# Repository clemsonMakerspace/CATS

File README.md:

CATS
====

The Clemson (Machinery) Access Tracking System, or CATS, is a [Creative Inquiry](http://www.clemson.edu/academics/programs/creative-inquiry/) project at Clemson University.

The goal of the project is to come up with an open-source system that can track and control machine access
at the Makerspaces on the campus.  As we work on the design process, we document our progress in our blog,
which you can find [here](http://ci.clemson.edu/blogs/cats/).

----

### Dependencies

This is a Python 3.x program dependent on the following libraries:
   1. `sys` - Python sys Libary
   2. `time` - Python time library
   3. `pymysql` - Python MySQL client
   4. `datetime` - Python datetime library
   5. `os` - Python os library (Python operating system interface)
   6. `RPi.GPIO` - package for controlling Rasberry Pi GPIO
   7. `string` - Python string library
   8. `InputDevice from evdev` - function from evdev package for Linux inputs
   9. `select from select` - Python select function from select library
   
These dependencies can be installed with the 'setup.sh' shell script found within.

### Configuration

TODO

### Usage

TODO

### License

The Clemson (Machinery) Access Tracking System is free software: you can 
redistribute it and/or modify it under the terms of the GNU Lesser General 
Public License as published by the Free Software Foundation, either version 
3 of the License, or (at your option) any later version.

The Clemson (Machinery) Access Tracking System is distributed in the hope 
that it will be useful, but WITHOUT ANY WARRANTY; without even the implied 
warranty of MERCHANTABILITY or FITNESS FOR A PARTICULAR PURPOSE.  See the
GNU Lesser General Public License for more details.

You should have received a copy of the GNU Lesser General Public License
along with this program.  If not, see <http://www.gnu.org/licenses/>

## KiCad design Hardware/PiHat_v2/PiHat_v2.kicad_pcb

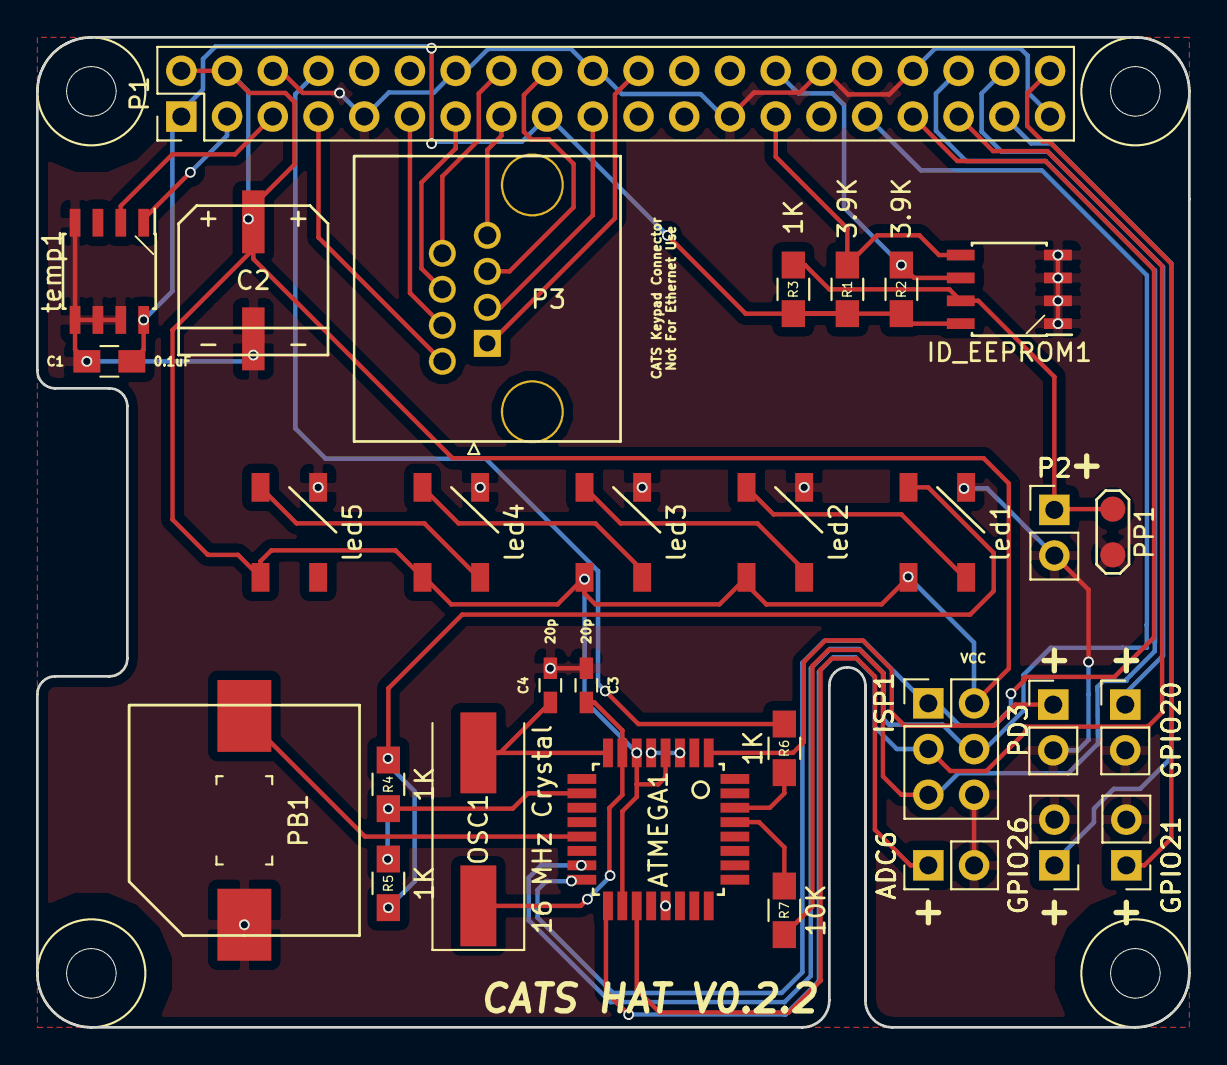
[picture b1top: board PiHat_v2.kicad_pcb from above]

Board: 2 copper layers, 64.0 x 55.0 mm, 35 parts (0 on the bottom side), 37 nets.

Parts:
ADC6: aux_conn; Pin_Header_Straight_1x02_Pitch2.54mm
ATMEGA1: ATMEGA328P-A; ATMEGA328P
C1: 0.1uF; C_0805_HandSoldering
C2: 1000uF; AluCap_8mmDia_Nichicon
C3, C4: 20p; C_0603_HandSoldering
GPIO20, GPIO21, GPIO26: aux_conn; Pin_Header_Straight_1x02_Pitch2.54mm
ID_EEPROM1: CAT24C32; SOIC-8_3.9x4.9mm_Pitch1.27mm
ISP1: ISP; Pin_Header_Straight_2x03_Pitch2.54mm
MountHole1, MountHole2, MountHole3, MountHole4: CONN_01X01; raspiMountingHole
OSC1: 16 MHz Crystal; Crystal_SMD_HC49-SD
P1: RPiGPIO; Pin_Header_Straight_2x20_Pitch2.54mm
P2: CONN_01X02; Pin_Header_Straight_1x02_Pitch2.54mm
P3: CONN_01X08; Keypad_Ethernet
PB1: Piezo; Piezo_CT-1205h-smt
PD3: aux_conn; Pin_Header_Straight_1x02_Pitch2.54mm
PP1: horizTest; Test_Point_2Pads
R1, R2: 3.9K; R_0805_HandSoldering
R3, R4, R5, R6: 1K; R_0805_HandSoldering
R7: 10K; R_0805_HandSoldering
led1, led2, led3, led4, led5: Neo_LED_RGB_IC; Neo_RGB_LED
temp1: LM75BD; SOIC-8_3.9x4.9mm_Pitch1.27mm

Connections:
+3V3: C1.1, ID_EEPROM1.8, P1.1, P1.17, R1.1, R2.1, R3.1, temp1.8
+5V: ATMEGA1.4, ATMEGA1.6, ATMEGA1.18, C2.1, ISP1.2, P1.2, P1.4, led1.VDD, led2.VDD, led3.VDD, led4.VDD, led5.VDD
/ADC6: ADC6.1, ATMEGA1.19
/GPIO2: P1.3, temp1.1
/GPIO3: P1.5, temp1.2
/GPIO4: P1.7, P3.2
/GPIO6: ATMEGA1.15, ISP1.4, P1.31
/GPIO10: P1.19, P3.3
/GPIO13: ATMEGA1.16, ISP1.1, P1.33
/GPIO16: ISP1.5, P1.36, R7.1
/GPIO17: P1.11, P3.4
/GPIO19: ATMEGA1.17, ISP1.3, P1.35
/GPIO20: GPIO20.1, P1.38
/GPIO21: GPIO21.1, P1.40
/GPIO22: P1.15, P3.7
/GPIO23: P1.16, P3.8
/GPIO24: P1.18, P3.5
/GPIO25: P1.22, P3.1
/GPIO26: GPIO26.1, P1.37
/GPIO27: P1.13, P3.6
/ID_SC: ID_EEPROM1.6, P1.28, R2.2
/ID_SD: ID_EEPROM1.5, P1.27, R1.2
/PB1: ATMEGA1.13, PB1.1
/PD3: ATMEGA1.1, PD3.1
/PD6: R4.1, R5.1, led1.DIN
/UART_TXD: P1.8, R6.1
GND: ADC6.2, ATMEGA1.3, ATMEGA1.5, ATMEGA1.21, C1.2, C2.2, C3.1, C4.1, GPIO20.2, GPIO21.2, GPIO26.2, ID_EEPROM1.1, ID_EEPROM1.2, ID_EEPROM1.3, ID_EEPROM1.4, ISP1.6, P1.6, P1.9, P1.14, P1.20, P1.25, P1.30, P1.34, P1.39, P2.2, PB1.2, PD3.2, PP1.1, led1.VSS, led2.VSS, led3.VSS, led4.VSS, led5.VSS, temp1.4, temp1.5, temp1.6, temp1.7
unnamed: ATMEGA1.7, C3.2, OSC1.1
unnamed: ATMEGA1.8, C4.2, OSC1.2
unnamed: ATMEGA1.10, R4.2, R5.2
unnamed: ATMEGA1.29, R7.2
unnamed: ATMEGA1.30, R6.2
unnamed: ID_EEPROM1.7, P2.1, PP1.2, R3.2
unnamed: led1.DOUT, led2.DIN
unnamed: led2.DOUT, led3.DIN
unnamed: led3.DOUT, led4.DIN
unnamed: led4.DOUT, led5.DIN

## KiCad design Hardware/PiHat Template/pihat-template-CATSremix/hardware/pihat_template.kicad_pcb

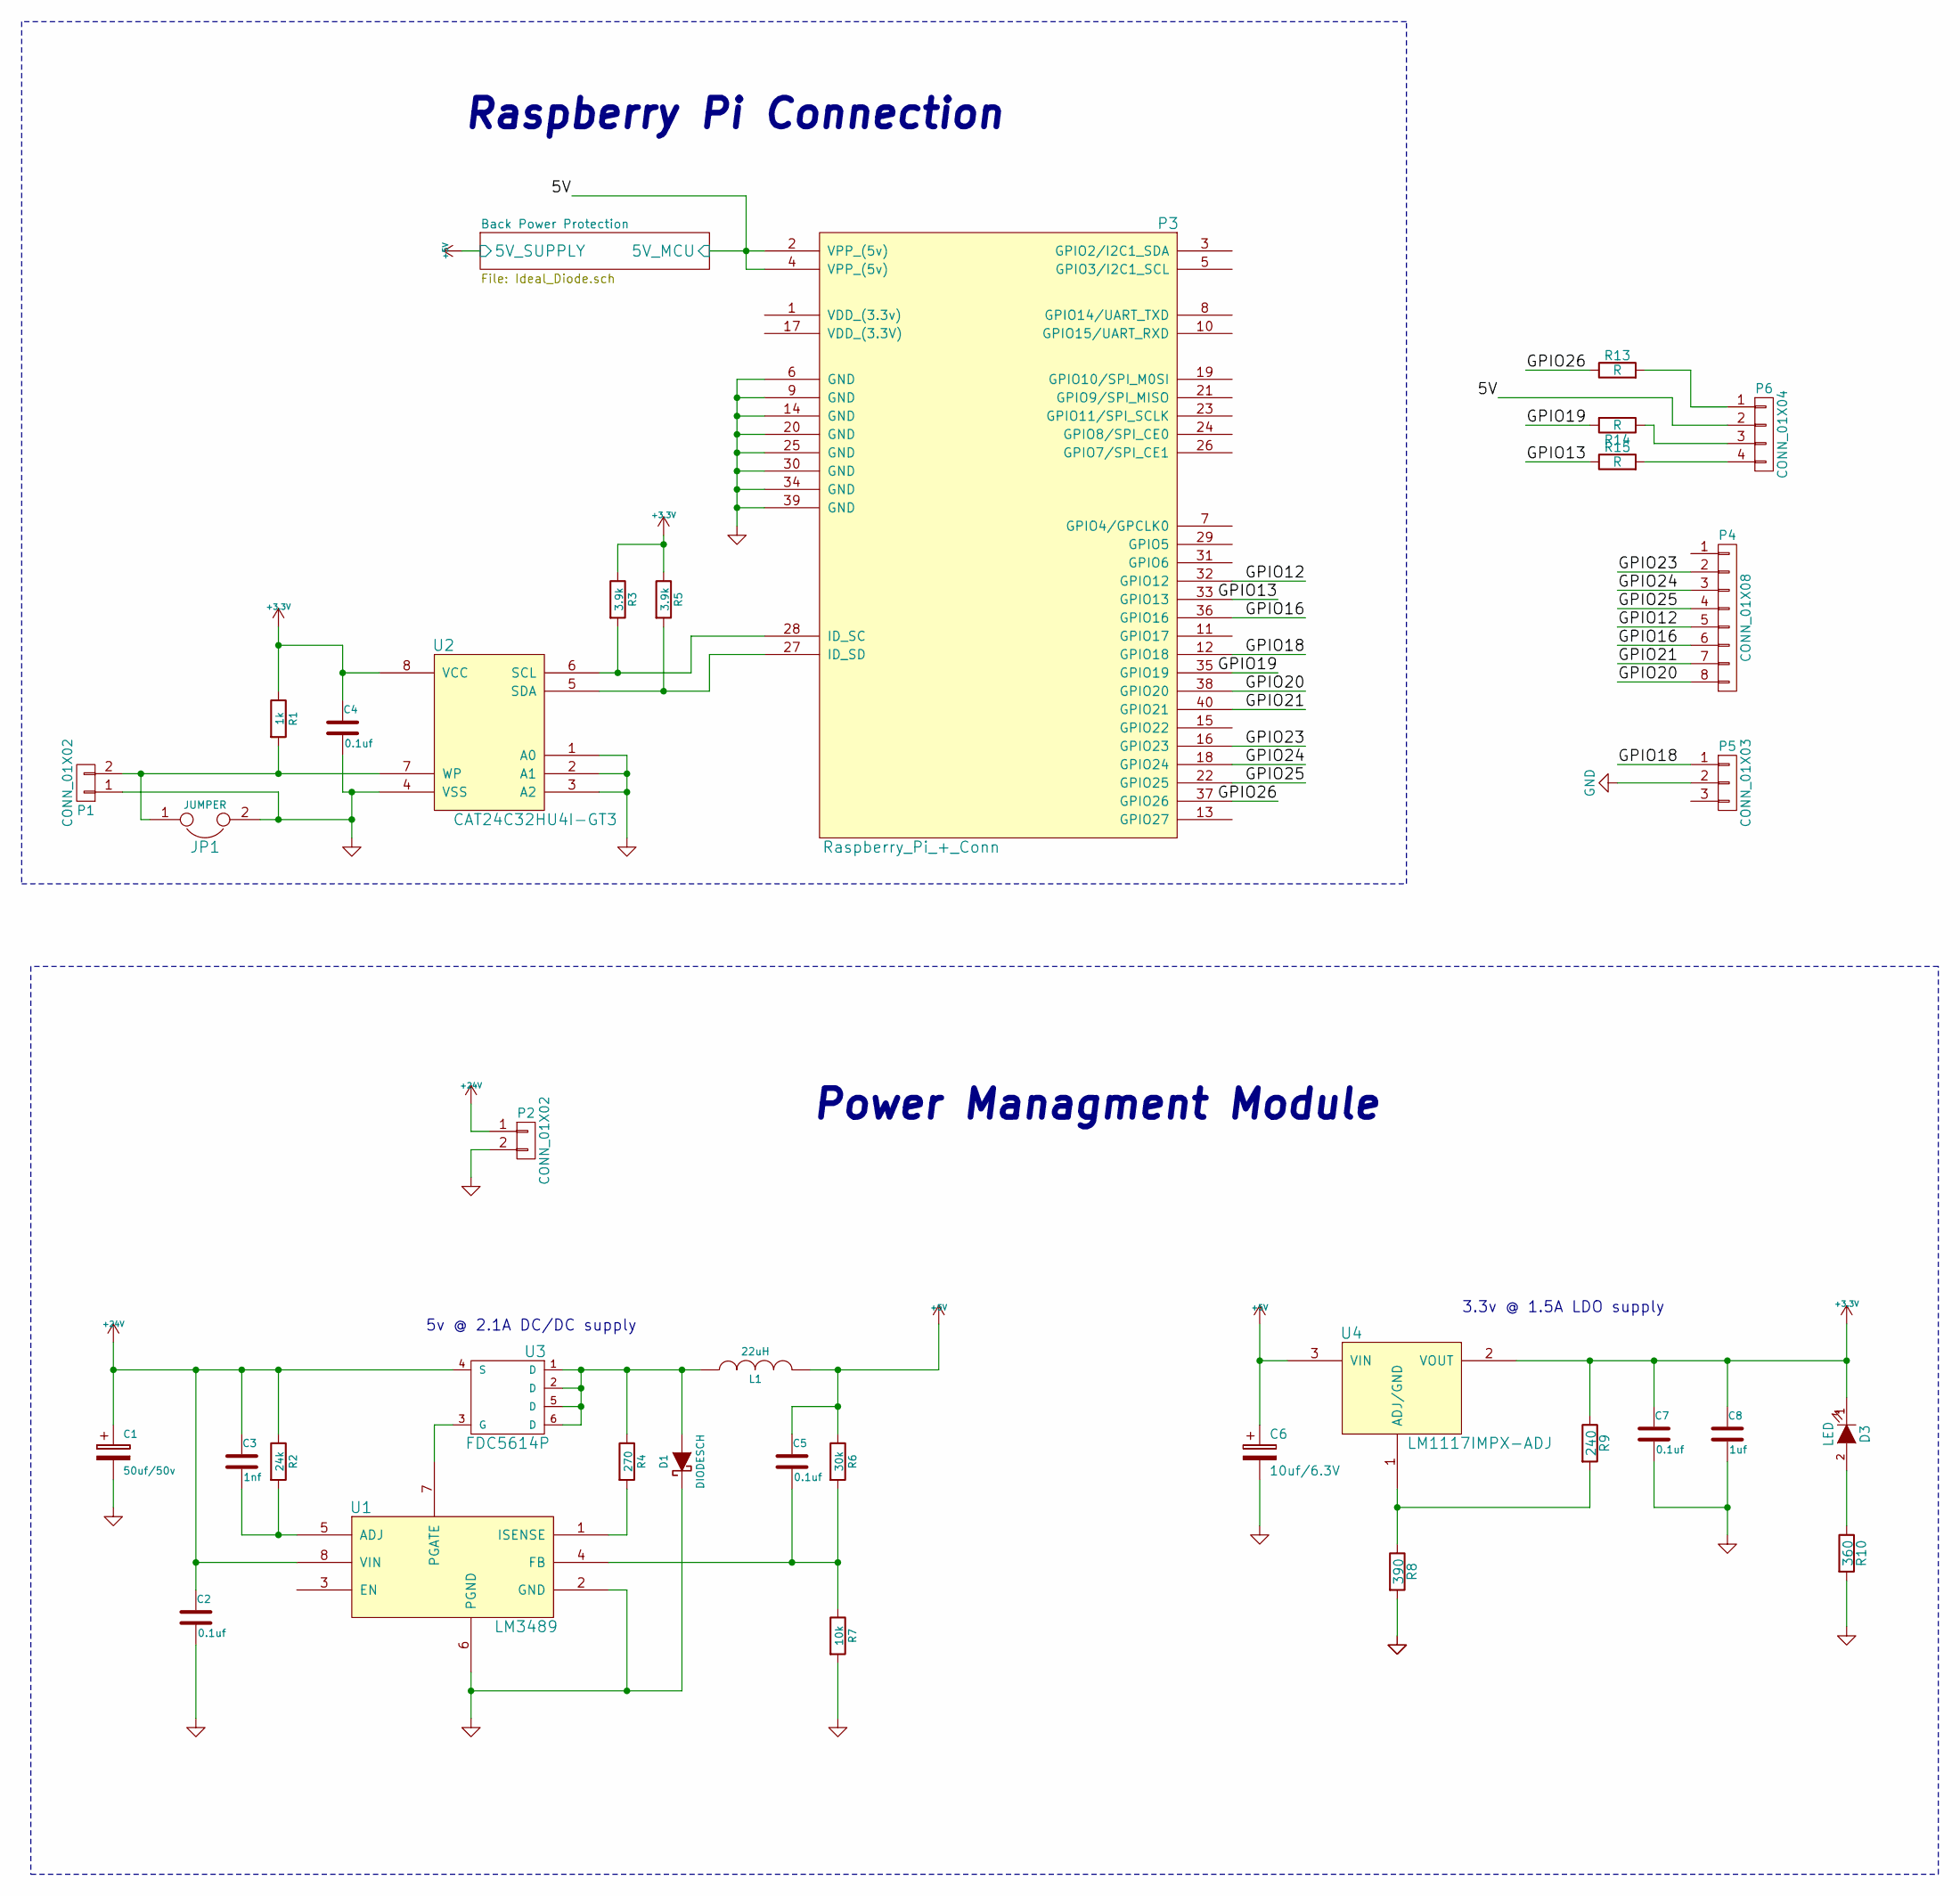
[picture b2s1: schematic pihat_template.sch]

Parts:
C1: 50uf/50v; c_elec_6.3x7.7; Mouser Part No. 647-UUR1H470MCL6GS
C2, C4, C5, C7: 0.1uf; c_0402; Mouser Part No. 810-C1005X5R1H104K
C3: 1nf; c_0402; Mouser Part No. 810-C1005C0G2A102J5C
C6: 10uf/6.3V; c_elec_4x5.3; Mouser Part No. 5985-AVS16V100-F
C8: 1uf; c_0402; Mouser Part No. 810-C1005X5R1H104K
D1: DIODESCH; do214aa; Mouser Part No. 512-MBRS140
D3: LED; Led_0603; Mouser Part No. 743-HT-191USD
JP1: JUMPER; r_0603
L1: 22uH; inductor_smd_8x5mm; Mouser Part No. 652-SRN8040-220M
P1: CONN_01X02; pin_strip_2
P2: CONN_01X02; mkds_1,5-2; Mouser Part No. 651-1904383
P3: Raspberry_Pi_+_Conn; vasch_strip_20x2; Mouser Part No. 517-30340-6002
P4: CONN_01X08; Socket_Strip_Straight_1x08
P5: CONN_01X03; Socket_Strip_Straight_1x03
P6: CONN_01X04; Socket_Strip_Straight_1x04
R1: 1k; r_0402; Mouser Part No. 754-RR0510P-102D
R2: 24k; r_0402; Mouser Part No. 71-CRCW0402-24K-E3
R3, R5: 3.9k; r_0402; Mouser Part No. 71-CRCW04023K90FKED
R4: 270; r_0402; Mouser Part No. 667-ERJ-P6WJ271V
R6: 30k; r_0402; Mouser Part No. 594-MCT06030C3002FP5
R7: 10k; r_0402; Mouser Part No. 71-CRCW0603-10K-E3
R8: 390; r_0402; Mouser Part No. 594-MCT06030C3900FP5
R9: 240; r_0402; Mouser Part No. 754-RR0816P-241D
R10: 360; r_0402; Mouser Part No. 71-CRCW0603316RFKEB
R13, R14, R15: R; Resistor_Vertical_RM5mm
U1: LM3489; msoic-8; Mouser Part No. 926-LM3489MM/NOPB
U2: CAT24C32HU4I-GT3; tssop-8; Mouser Part No. 698-CAT24C32YI-GT3
U3: FDC5614P; sot23-6; Mouser Part No. 512-FDC5614P
U4: LM1117IMPX-ADJ; sot223; Mouser Part No. 926-M1117IMPXADJNOPB

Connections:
+3V3: C4.1, C7.1, C8.1, D3.1 (K), R1.1, R3.1, R5.1, R9.1, U2.8 (VCC), U4.2 (VOUT)
+5V: C5.1, C6.1, L1.2, R6.1, U4.3 (VIN); also elsewhere on the board
+24V: C1.1, C2.1, C3.1, P2.1, R2.1, U1.8 (VIN), U3.4 (S)
/5V: P3.2 (VPP_(5v)), P3.4 (VPP_(5v)), P6.2; also elsewhere on the board
/GPIO12: P3.32 (GPIO12), P4.5
/GPIO13: P3.33 (GPIO13), R15.1
/GPIO16: P3.36 (GPIO16), P4.6
/GPIO18: P3.12 (GPIO18), P5.1
/GPIO19: P3.35 (GPIO19), R14.2
/GPIO20: P3.38 (GPIO20), P4.8
/GPIO21: P3.40 (GPIO21), P4.7
/GPIO23: P3.16 (GPIO23), P4.2
/GPIO24: P3.18 (GPIO24), P4.3
/GPIO25: P3.22 (GPIO25), P4.4
/GPIO26: P3.37 (GPIO26), R13.1
GND: C1.2, C2.2, C4.2, C6.2, C7.2, C8.2, D1.1 (K), JP1.2, P1.1, P2.2, P3.6 (GND), P3.9 (GND), P3.14 (GND), P3.20 (GND), P3.25 (GND), P3.30 (GND), P3.34 (GND), P3.39 (GND), P5.2, R7.2, R8.2, R10.2, U1.2 (GND), U1.6 (PGND), U2.1 (A0), U2.2 (A1), U2.3 (A2), U2.4 (VSS); also elsewhere on the board
unnamed: C3.2, R2.2, U1.5 (ADJ)
unnamed: C5.2, R6.2, R7.1, U1.4 (FB)
unnamed: D1.2 (A), L1.1, R4.1, U3.1 (D), U3.2 (D), U3.5 (D), U3.6 (D)
unnamed: D3.2 (A), R10.1
unnamed: JP1.1, P1.2, R1.2, U2.7 (WP)
unnamed: P3.27 (ID_SD), R5.2, U2.5 (SDA)
unnamed: P3.28 (ID_SC), R3.2, U2.6 (SCL)
unnamed: P6.1, R13.2
unnamed: P6.3, R14.1
unnamed: P6.4, R15.2
unnamed: R4.2, U1.1 (ISENSE)
unnamed: R8.1, R9.2, U4.1 (ADJ/GND)
unnamed: U1.7 (PGATE), U3.3 (G)

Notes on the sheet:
Raspberry Pi Connection
Power Managment Module
5v @ 2.1A DC/DC supply
3.3v @ 1.5A LDO supply

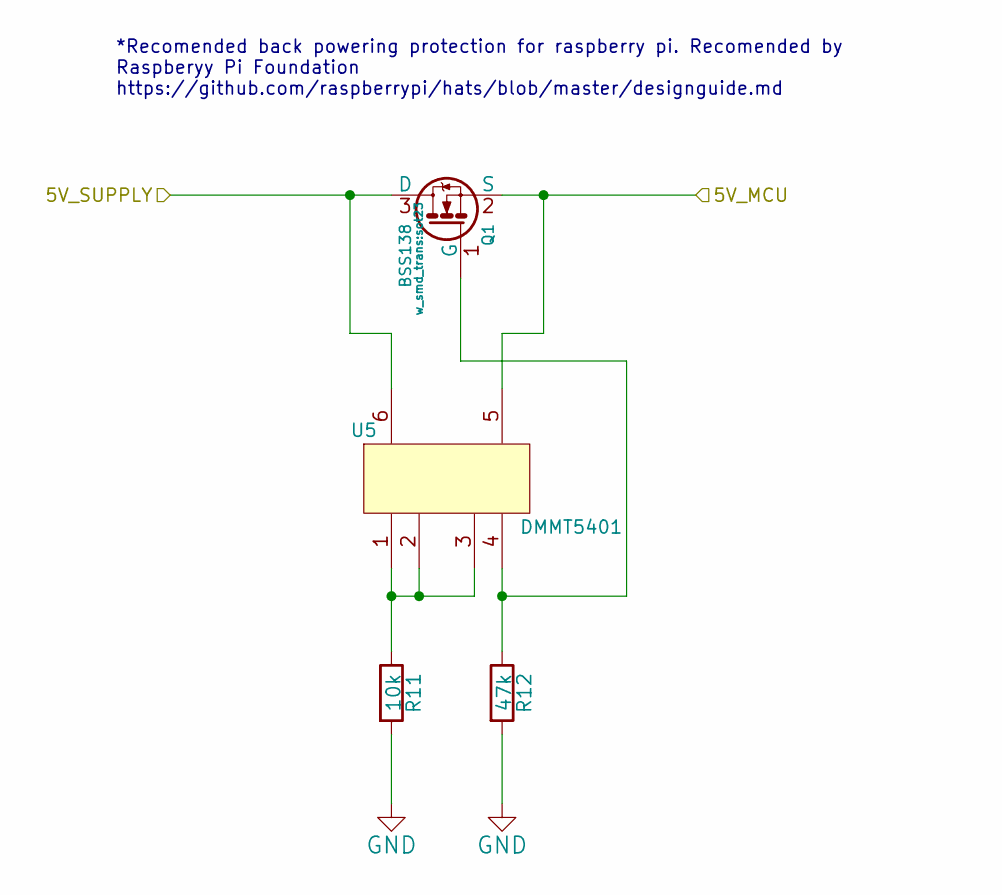
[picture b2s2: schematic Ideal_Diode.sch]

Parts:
Q1: BSS138; sot23; Mouser Part No. 621-DMG2305UX-13
R11: 10k; r_0402; Mouser Part No. 71-CRCW0402-10K-E3
R12: 47k; r_0402; Mouser Part No. 667-ERJ-2RKF4702X
U5: DMMT5401; sot23-6; Mouser Part No. 621-DMMT5401-7-F

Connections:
+5V: Q1.3 (D), U5.6; also elsewhere on the board
/5V: Q1.2 (S), U5.5; also elsewhere on the board
GND: R11.2, R12.2; also elsewhere on the board
unnamed: Q1.1 (G), R12.1, U5.4
unnamed: R11.1, U5.1, U5.2, U5.3

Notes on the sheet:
*Recomended back powering protection for raspberry pi. Recomended by Raspberyy Pi Foundation https://github.com/raspberrypi/hats/blob/master/designguide.md

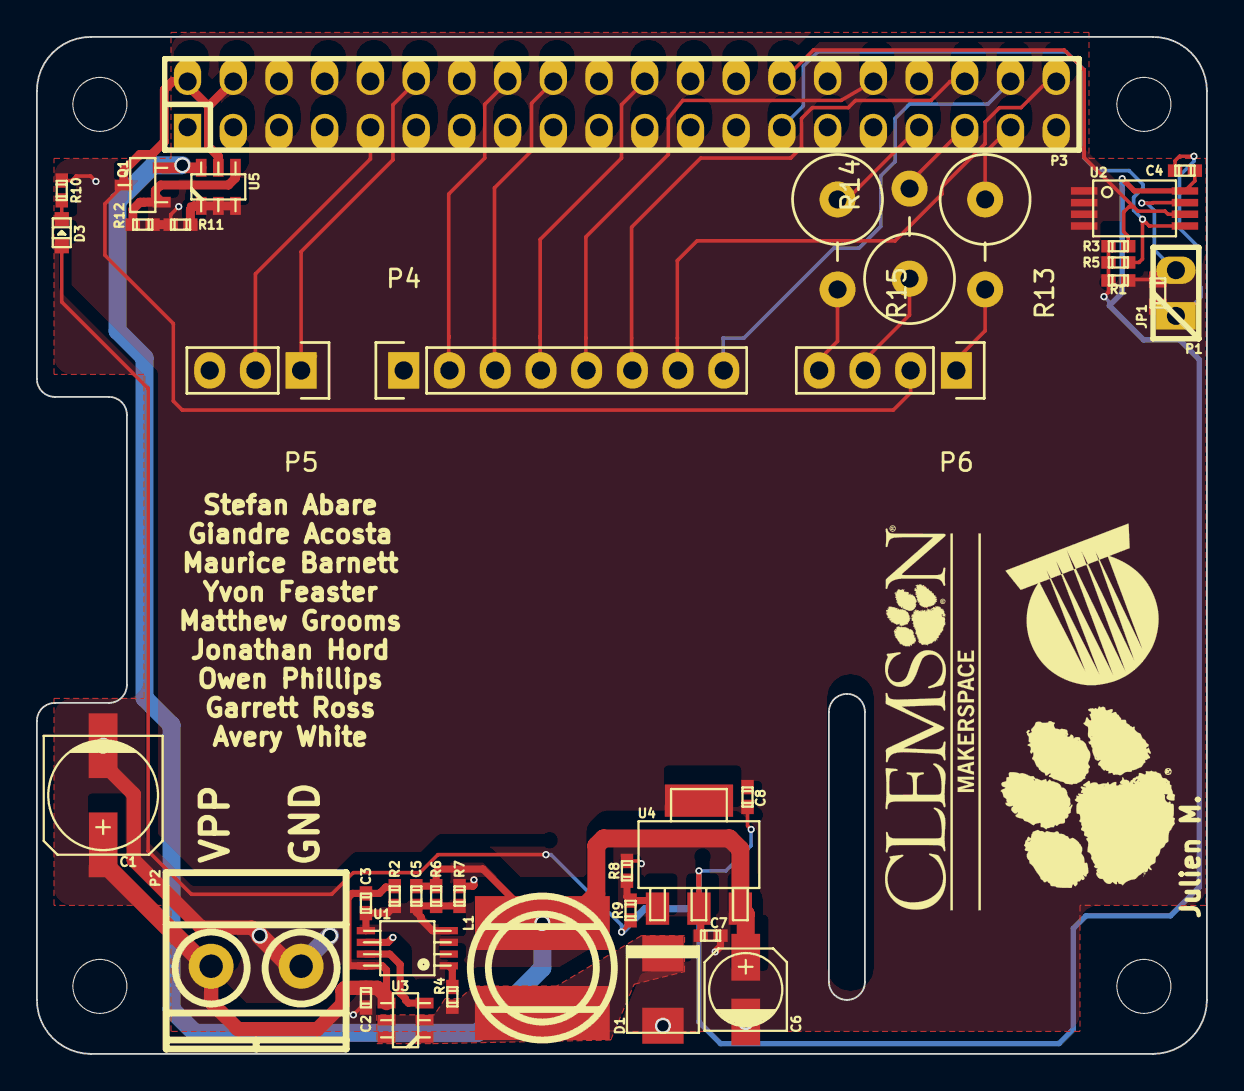
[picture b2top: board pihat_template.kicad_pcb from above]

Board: 2 copper layers, 65.0 x 56.5 mm, 39 parts (0 on the bottom side), 31 nets.

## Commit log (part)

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2016-10-05 Added Software Folder and setup script
2016-10-05 touching up on the script
2016-10-05 added more commands
2016-10-06 Correct Whitespace & Formatting
    I've removed some whitespace from the end of lines, as well as extra
    tabs on blank lines.
2016-10-06 added python3 rpi library command
2016-10-08 Hardware Info
    Added hardware data and diagrams.
2016-10-11 trying to print & type 4 keys without exiting
2016-10-11 Working keyboard matrix
2016-10-11 Add Newline to End of .gitignore
    Git isn't happy without a newline at the end of a text file.
    I've added one to make sure git is happy.
2016-10-11 added matrix folder and working code
2016-10-11 Hardware Information
    Added the three different schematics for the alpha prototype.
    Wiring Diagram, Wiring Schematic, and the Context Level Schematic.
2016-10-17 don't need the folder, just the code
2016-10-17 On and Off PowerSwitch Tail Control
2016-10-20 added working authentication code
2016-10-21 archived file containing the scanning/keypad code
2016-10-25 update of rpi scan
2016-10-25 Cleaning up the code
2016-10-25 Removed files
2016-11-01 user confirmation from SQL db
2016-11-01 Card reader and PIN update up and running
2016-11-10 Update to main.py
    Help it change to run.py.
2016-11-10 Added LED feedback
    Brice did this part
2016-11-10 Update run.py
    Makes the infinite loop look a little more professional.
2016-11-11 Remove ._*.py Files
    These files appear to be generated by OS X. They don't contain anything
    useful for our project and should therefore be removed.
2016-11-11 Ignore OS X Resource Forks
    OS X seems to be leaving behind these Resource Forks that are cluttering
    up the repo.
    They all start with ._*
2016-11-11 Remove Old on_off.py
    This class has been rewritten already, and this file appears to be a
    remnant of older times.
2016-11-11 Cleanup Readability of on_off.py
2016-11-12 Update on_off.py
    fixed code, added more comments.
2016-11-12 working main for ISAM prototype
2016-11-12 Remove Unecessary Main
2016-11-12 Implement LED Flash when Turning Power Off
2016-11-13 temp fix to user not authorized error
2016-11-14 Assume Yes When Installing through Apt-Get
2016-11-14 Move Pip Installs Lower
2016-11-24 Create ISAM Poster
2016-11-24 Created Hardware Folder and ISAM Poster included inside (#51)
    * temp fix to user not authorized error
    * Create ISAM Poster
    * ISAM Poster
    * Delete ISAM Poster
2016-12-13 Completed Enhancements (#53)
    G committed some sensitive information here. Hopefully these can be deleted.
    * Add files via upload
    * updated working ISAM prototype
    * update prototype
    * temp fix to user not authorized error
    * Create ISAM Poster
2017-01-13 Update main.py (#59)
    This will be necessary until we resolve #60.
2017-01-14 Update ErrorSQL.py (#58)
    * Update ErrorSQL.py
    * Update ErrorSQL.py
2017-01-14 Added authentication diagram (#67)
    Simple flow chart that documents how main.py tries to check to see if a
    user is authenticated.
2017-01-16 Add files via upload
    Added hardware files to the repository.
2017-01-16 Add files via upload
    Fritzing breadboard layout files
2017-01-17 Remove extraneous dev code
2017-01-17 Remove Git Diff from Setup
2017-01-17 Correct funky indentation
2017-01-17 Test for thor
2017-01-17 Update README.md
    Added a period to the end of the sentence
2017-01-20 im adding this
2017-01-20 Fixed the Invalid PIN re-prompt bug
2017-01-20 reset timer after key pressed
2017-01-22 program would quit out of nowhere, removed a line and its all good
2017-01-23 starting to implement optional two-factor authentication
2017-01-25 Added Audio effect to successful & unsuccessful login
2017-01-25 PiHat_v2 - A New Hope
    Hoping to cut out a lot of the bullshit from the PiHAT designs. I've
    designed the edge cuts from the specifications listed in the [HAT board
    specification.](https://github.com/raspberrypi/hats/blob/master/hat-board-mechanical.pdf)
2017-01-25 Correct EEPROM Schematic - Add Pin Numbers
2017-01-25 Complete First Draft of Routing
2017-01-25 Implement Mounting Holes & Remove Improper Keepout Areas
    This board should be electrically sound - and looks to me like it has
    all the right parts at first glance. There are some definite silk-screen
    improvements that can be made, however.
2017-01-25 One final thing . . .
    Sorry Stefan.
2017-01-30 Proposed Meeting Minutes for Team Leads 2017-01-30
2017-01-31 Added brief config file
    Will be implementing it into the actual code now.
2017-01-31 Update config.cfg
    Added new line, mind explaining why the new line is necessary?
2017-01-31 Commenting Horrific SQL Queries
2017-02-01 requirements.txt v0.1
    Attempted to create a requirements.txt file. From what I could read, it consists of the arguments in the commands for setup.sh (the package names). Not entirely sure if any of it is right
2017-02-01 Update requirements.txt v0.2
    I assume that we are using the most recent versions of these
2017-02-02 -Web admin files
2017-02-02 Team Leads 2017-02-01 and SQL Error fixes
2017-02-03 New Schematic for PiHat
2017-02-07 finished first test
2017-02-07 Added second test!
2017-02-07 ADDED A THIRD ONE OMG
2017-02-08 Update requirements.txt (#112)
2017-02-15 Meeting Minutes for 2017-02-15
2017-02-16 Finished PiHat v2 Design
2017-03-01 Update AuthenticationSQL.py
    Okay so I fixed how we get the stuffs from the SQL. There were a few things that were pretty screwy. So now we look up "authType" using "PiHostname" in the SQL, then look up the variable that authTyp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
2017-03-02 Optional Keypad Implemented
2017-03-13 Added CATS Enclosure Files for SolidWorks
    CATS Enclosure V0.2
2017-03-13 Dimensioned Drawings
    Dimensioned Drawings of the V0.2 enclosure + Exploded view.
2017-04-05 PiHat Completion
    References for footprints are placed and named more efficiently. The pi
    header footprint is now on the back of the board and all connections to
    it were corrected. Added "+"s to the AUX references to show which side
    is positive and those reference texts are now what GPIO pin connects to
    it. Some footprints that are for components that are polarized or need
    to be placed a certain way were redone to show the orientation of the
2017-04-05 Revert "PiHat Completion"
    This reverts commit 6738365f23747a299ba35bc740daefcfdec640b0.
2017-04-05 Optional Keypad Implemented (#123)
    * Optional Keypad Implemented
    * Update AuthenticationSQL.py
    cleaning up the code a bit.
    * Update AuthenticationSQL.py
    * Update AuthenticationSQL.py
    * Update AuthenticationSQL.py
2017-04-11 New piHat
2017-04-12 Draft Logging Temperature
2017-04-13 Thor's Base PCB Design
    This is the design that Thor attempted to commit to github in PR #130.
    It consists of the 'Finished PiHAT v2 Design', the 'Neopixel Footprint
    Fix', and the addition of our names on the silkscreen.
2017-04-13 Implement CI, Makerspace, Paw Logo on PiHAT
2017-04-13 Redraw Fill Zones on PiHAT v0.2.1
    Whoops - Forgot to redraw the fill zones. That's been remedied!
2017-04-18 Simple Bash Script to test SSH Tunnel for SQL Nodes
2017-04-20 removed python2.7 (#135)
2017-04-25 SQL Statements have been modified and GPIO pins
2017-04-26 Preliminary NeoPixel Support
    Accessing the Neopixels is tough.
    - This file has to be run as root due to the direct memory access.
    - Colors are listed as GBR despite documentation stating otherwise
    - Several global variables are used in this module - should not be like tihs
    - Synchronizing the beeping and LEDs still needs to be done
    - This needs to be tested within the CATS ecosystem
2017-04-26 why is G writing commits to my repo? Fixes Neopixel Support Commit after #138 (#139)
    * Simple Bash Script to test SSH Tunnel for SQL Nodes
    * SQL Statements have been modified to fit the new SQL Database
    * SQL Statements have been modified and GPIO pins
    * Preliminary NeoPixel Support
    Accessing the Neopixels is tough.
    - This file has to be run as root due to the direct memory access.
2017-04-26 stuff
2017-04-26 getting ready for maker
2017-04-26 Getting Ready For Maker Day (#140)
    * starting to implement optional two-factor authentication
    * starting to implement optional two-factor authentication
    * Adding audio files
    * Added Audio effect to successful & unsuccessful login
    * added the main components that I know of
    * deleted function (will implement later if needed) and removed pygame from requirements.txt and header
2017-04-27 Changed a word in ErrorSQL.py file (#142)
    * starting to implement optional two-factor authentication
    * starting to implement optional two-factor authentication
    * Adding audio files
    * Added Audio effect to successful & unsuccessful login
    * added the main components that I know of
    * deleted function (will implement later if needed) and removed pygame from requirements.txt and header
2017-04-27 on_off was wiggity wack
2017-04-27 Commented Structure for Piezo & Flash - Sped Up RPI Card Scan
2017-04-27 Fixed toggle button CSS for Brad
2017-05-13 Add nose to requirements.txt
2017-05-13 Correct Nose Command
2017-05-13 LED & Relay Info in Config
2017-05-14 Refactor on_off.py
2017-05-14 Update Imports for led and buzzer
2017-05-14 Update Indentation in Main
2017-05-14 Rudimentary Testing
2017-05-28 New PCB With ATMEGA
    This includes installing the ATMEGA chip for controlling the neopixel
    and piezo buzzer. A new piezo for louder sound was added as well.
2017-06-01 SQL Refactoring & Closes #141 (#147)
    * Update configparser version
    * Add nose to requirements.txt
    * Travis-CI Support
    * Correct Nose Command
    * Update Commenting in rpiCardScan
    * LED & Relay Info in Config
2017-06-01 Remove Unnecessary Git Merge Lines
    smh @thorbrockman
2017-06-14 Correct Extra Blank Lines in Schematic
2017-06-14 Increment Version Number on PCB
2017-06-14 Update KiCad Project Timestamp
2017-06-14 Re-draw Copper Pours
2017-06-16 Fixes Thor's Misery (#151)
    * Update README.md
    Added a period to the end of the sentence
    * New Schematic for PiHat
    * Finished PiHat v2 Design
    * Neopixel Footprint Fix
    Rearranged the neopixel terminals to correctly mount it. Moved around
2017-06-17 Schematic for Neopixel Chain & ISP Program Header
    I've chained 5 Neopixels and added an ISP header for the ATMEGA.
2017-06-17 Add PWR_FLAG to Schematic
    Solves "Pin connected to some other pins but no pin to drive it ERC
    error.
2017-06-17 Take AREF off 5v for ATMEGA
2017-06-17 Update Netlist
2017-06-17 Regenerate Netlist with new footprints
2017-06-17 Move to SMT Piezo Buzzer
2017-06-17 Replace Mounting Holes and RPiGPIO Header
2017-06-17 Position Neopixel Strip
2017-06-17 Adjust silkscreen layer in footprints to display pin #s
2017-06-17 Tweak Silkscreen of Resistors and Capacitors
2017-06-17 Adjust Silkscreen Layout on PCB
2017-06-19 Implement AluCap in PCB
2017-06-19 Built the BOM
2017-06-19 YASA - Yet Another Silkscreen Adjustment
2017-06-19 Update Version Number of PiHat
2017-06-19 Fix BOM Whitespace
2017-06-20 Forgot the shunt jumpers
2017-06-28 Serial code for Pi to ATMEGA

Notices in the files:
Hardware/PiHat Template/pihat-template-CATSremix/hardware/pihat_template.kicad_pcb:
License: CERN OHL V1.2
CERN OHL V1.2
